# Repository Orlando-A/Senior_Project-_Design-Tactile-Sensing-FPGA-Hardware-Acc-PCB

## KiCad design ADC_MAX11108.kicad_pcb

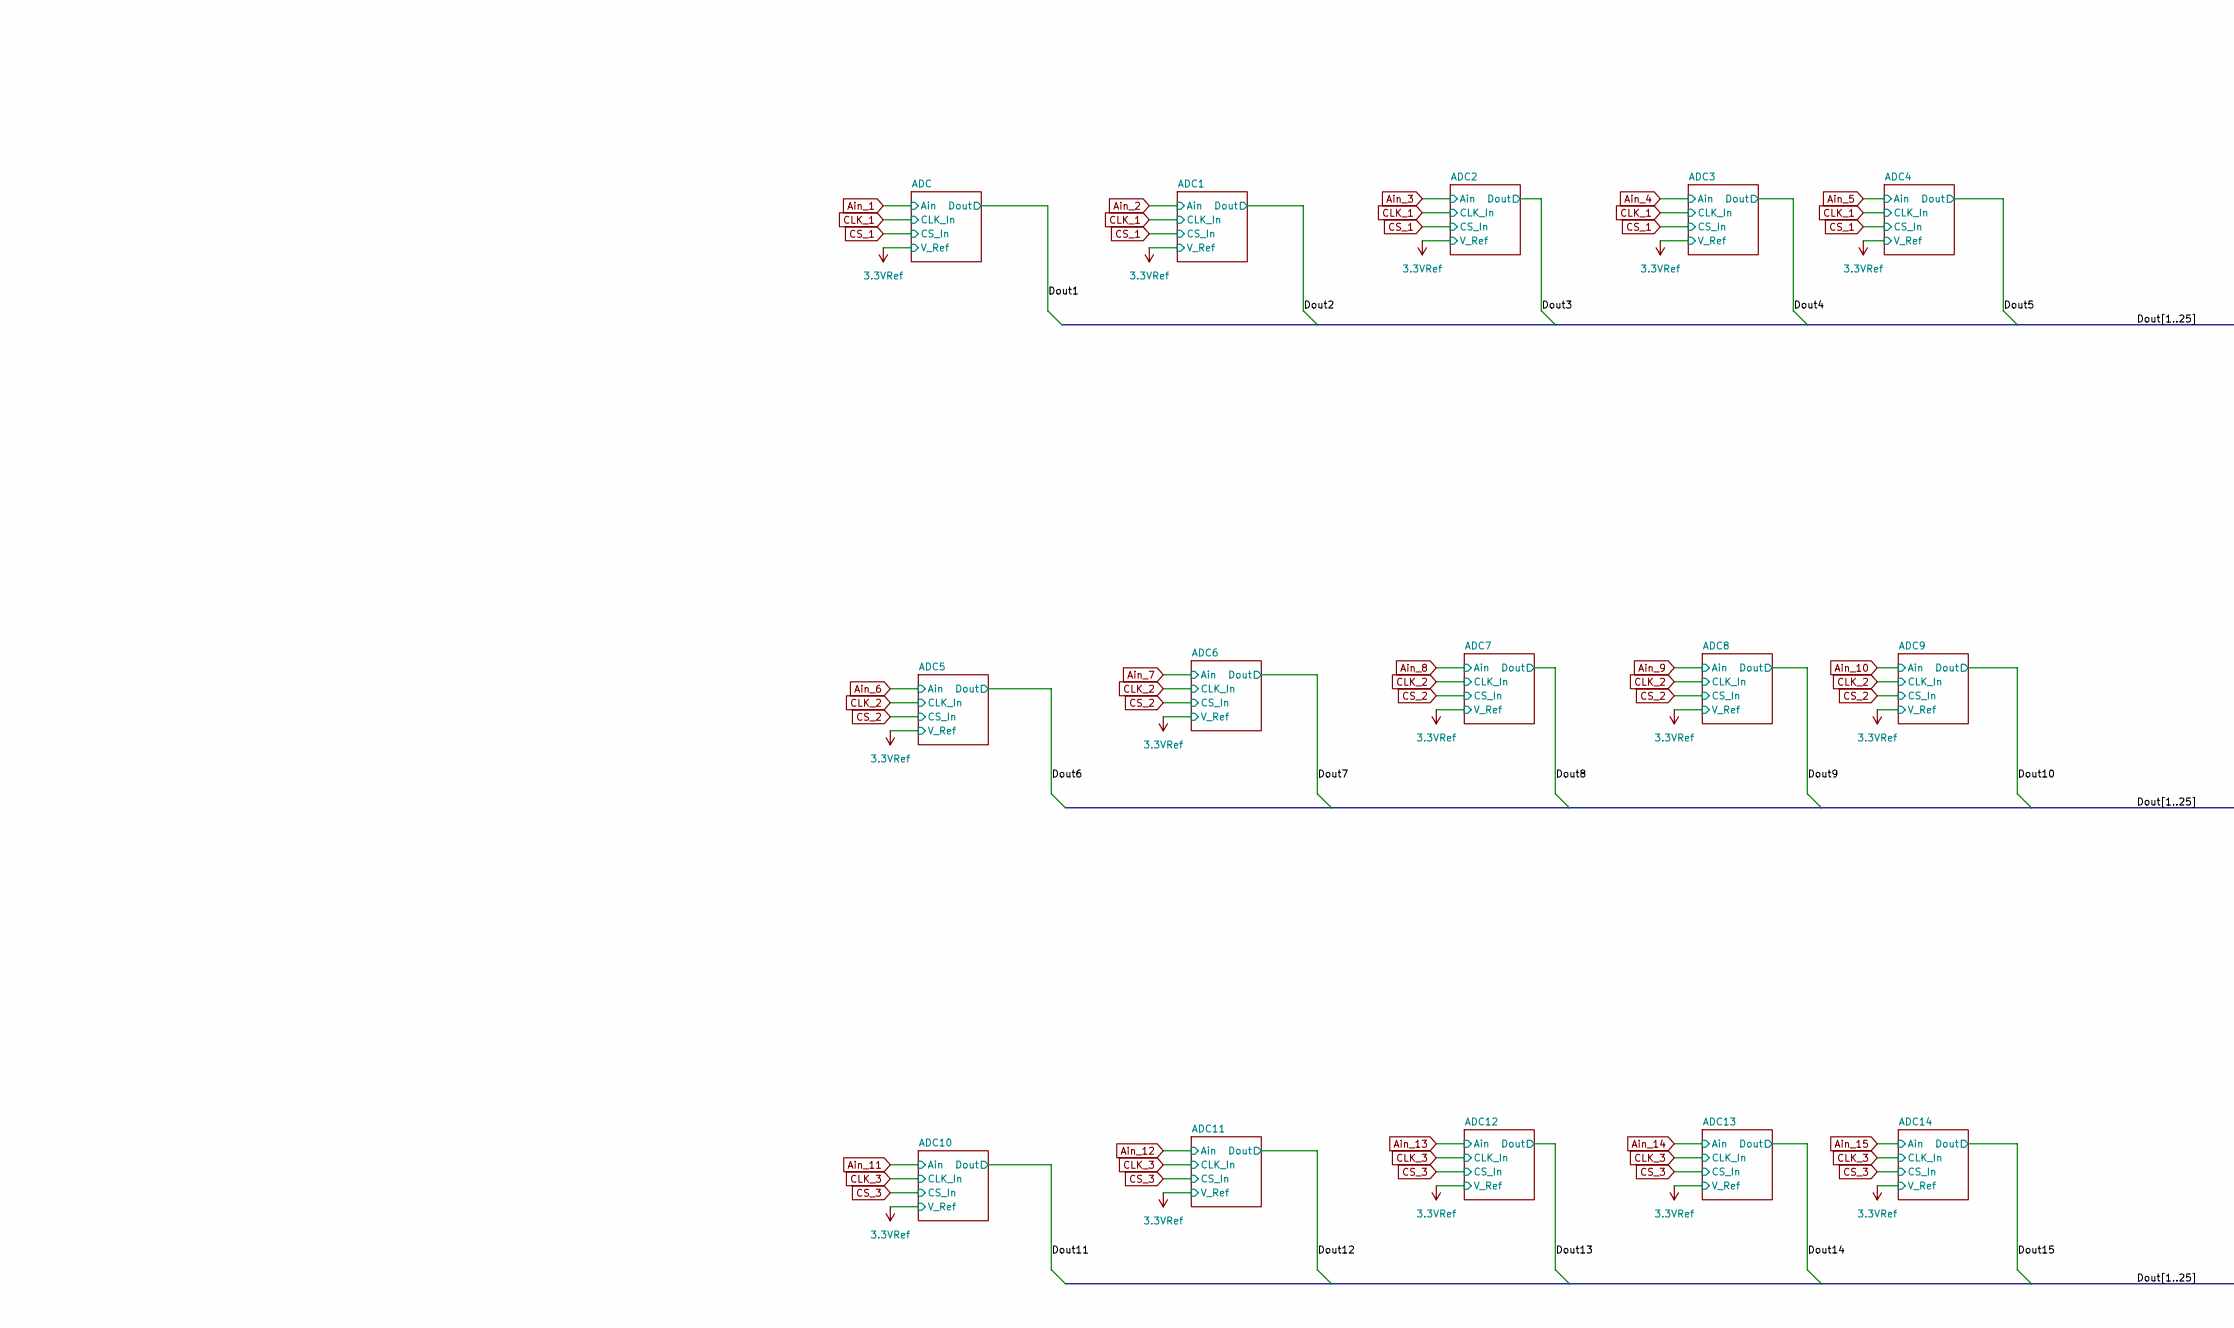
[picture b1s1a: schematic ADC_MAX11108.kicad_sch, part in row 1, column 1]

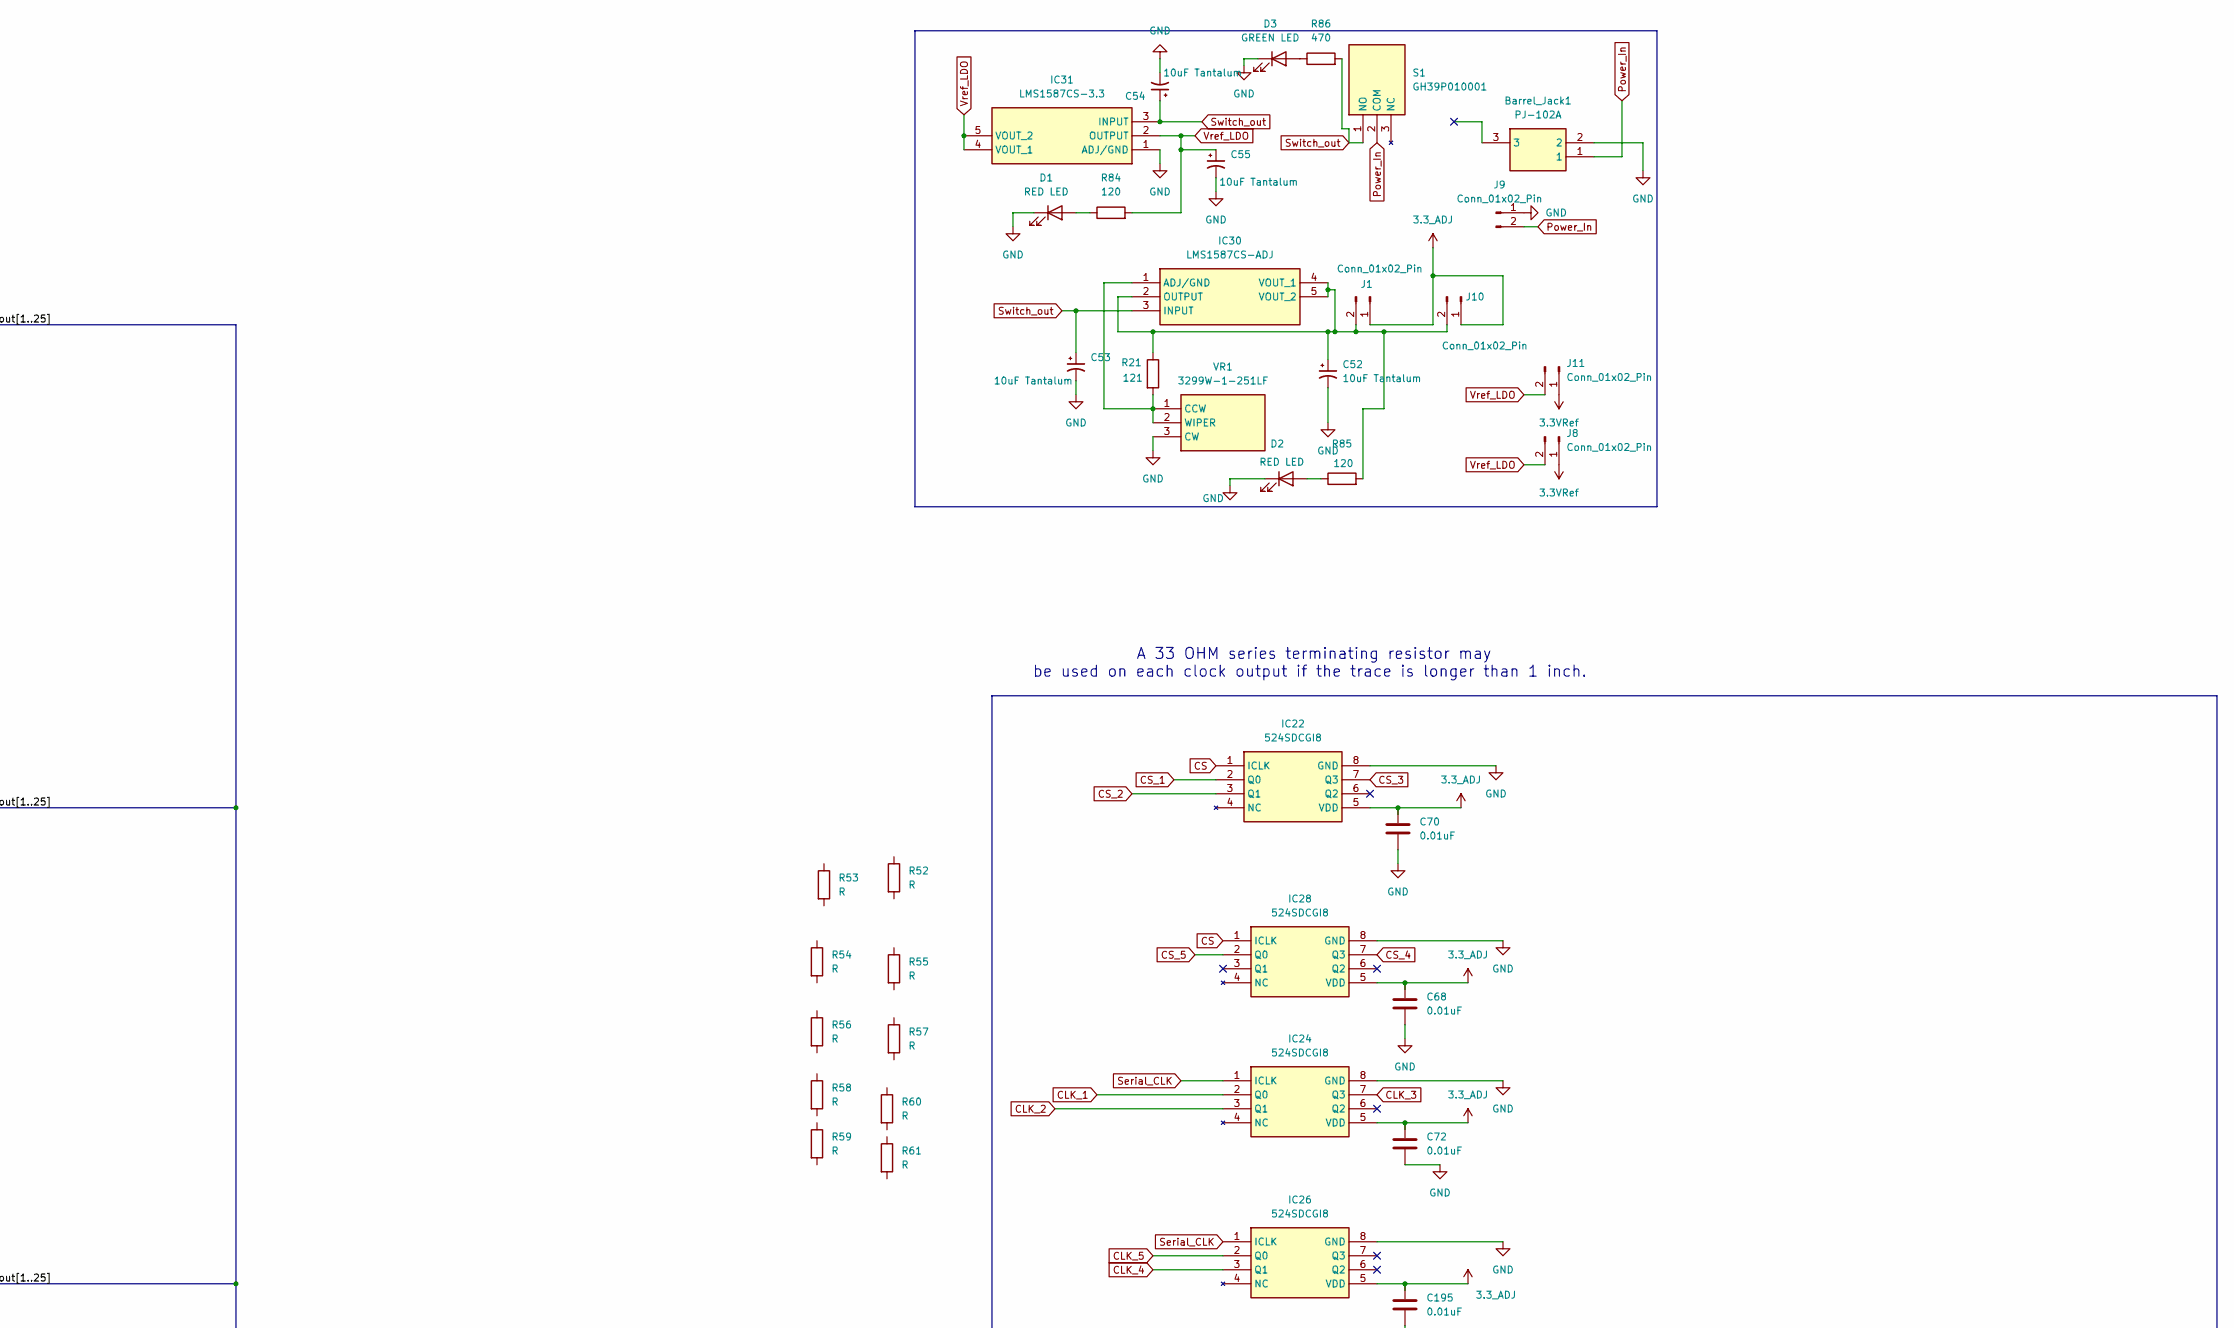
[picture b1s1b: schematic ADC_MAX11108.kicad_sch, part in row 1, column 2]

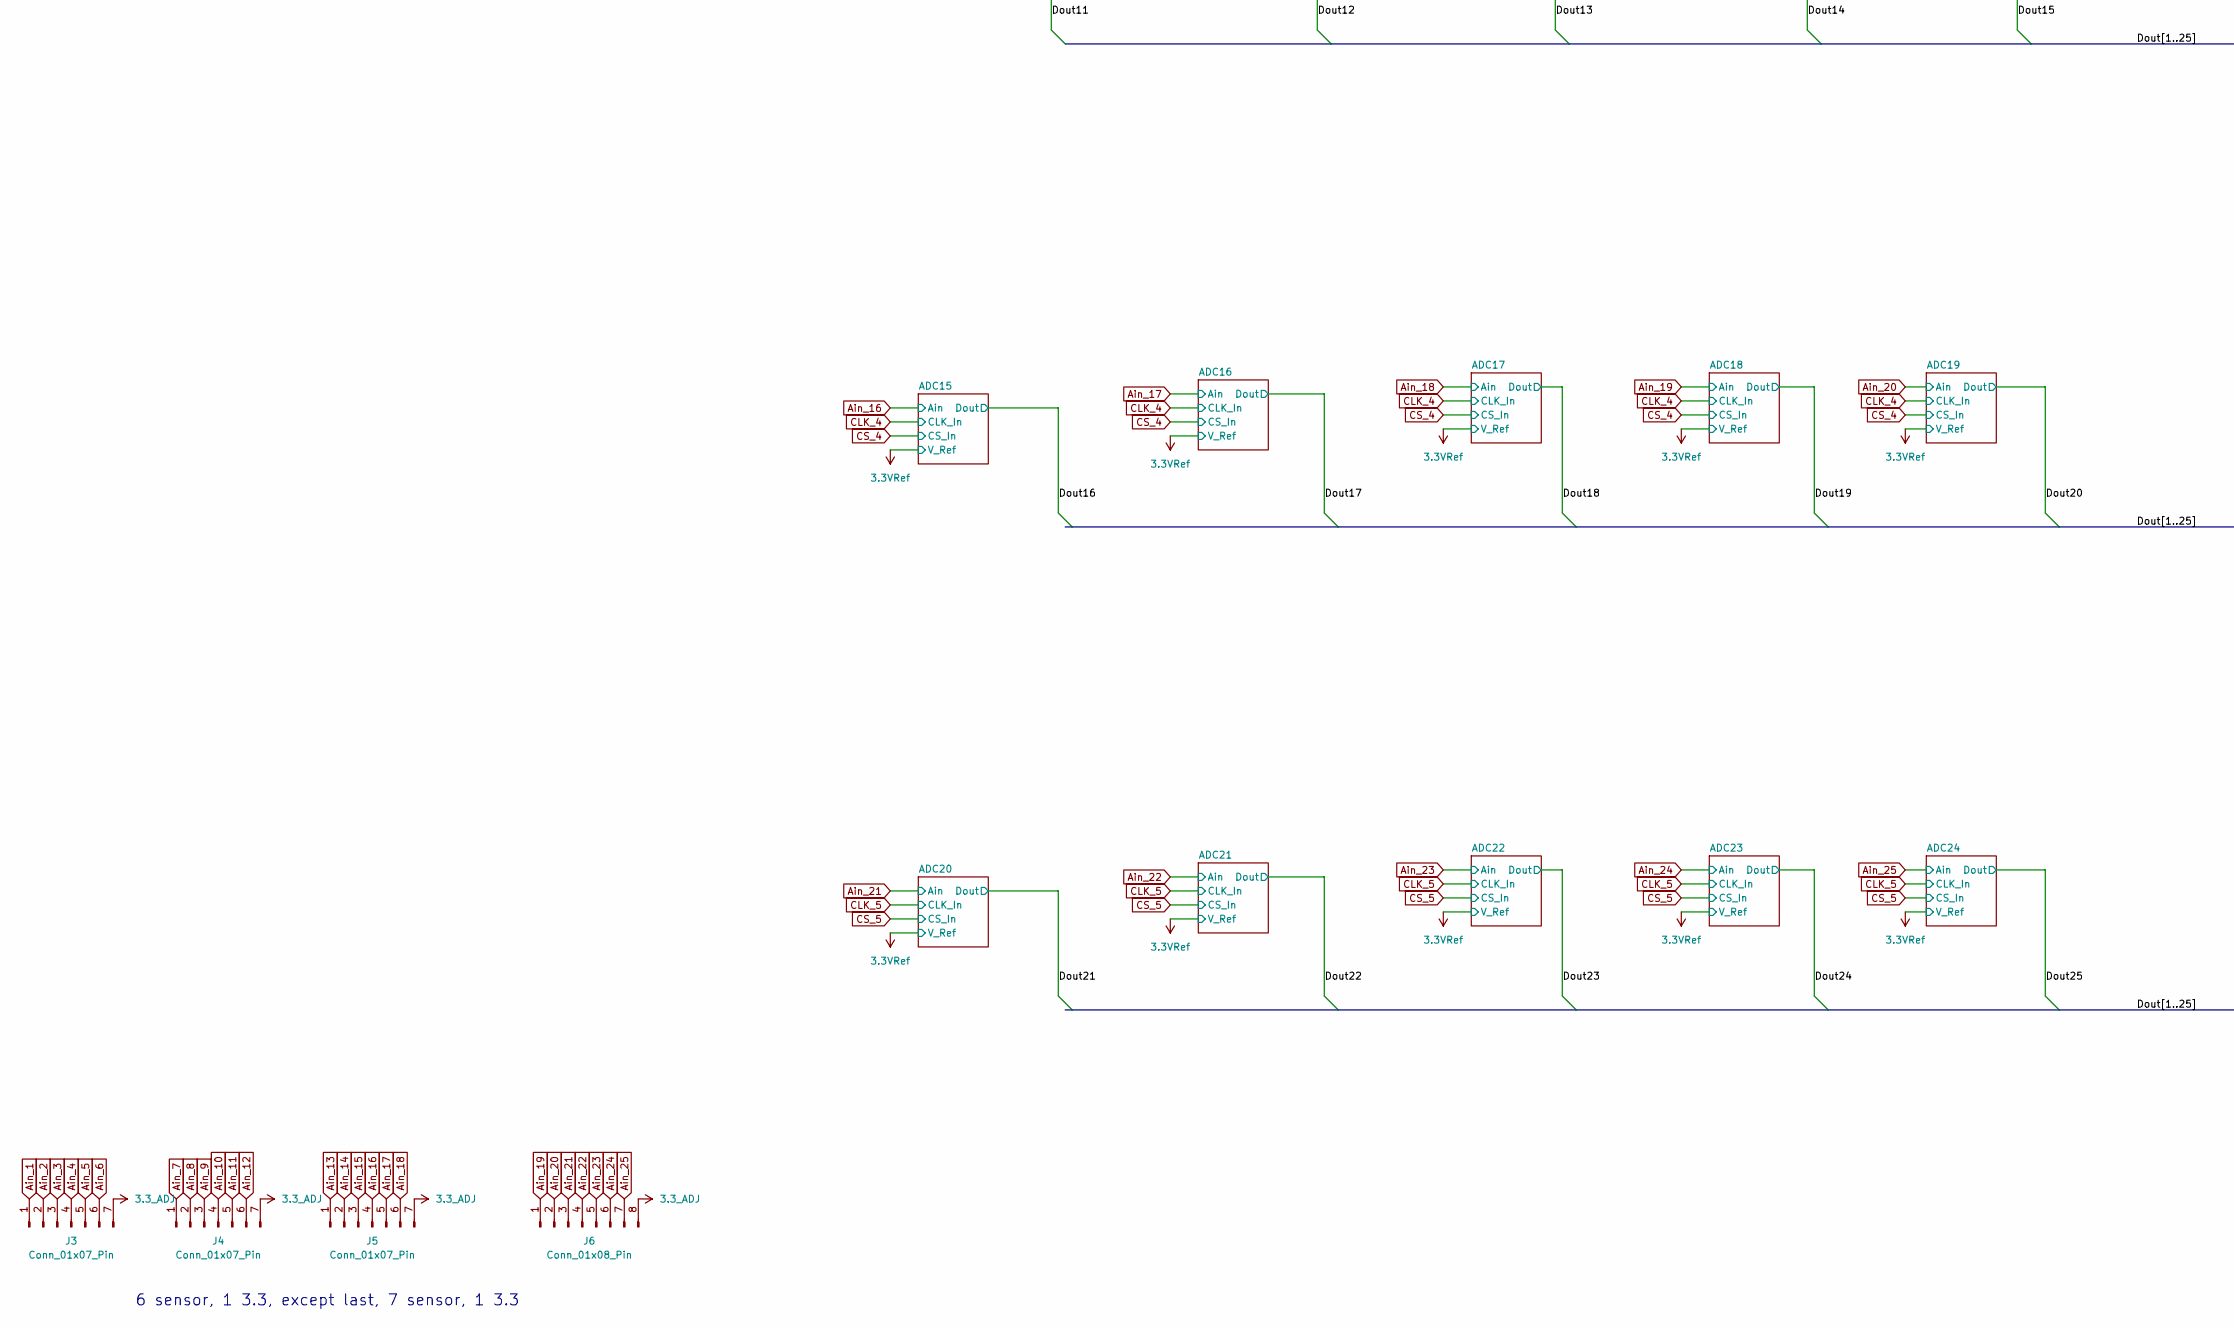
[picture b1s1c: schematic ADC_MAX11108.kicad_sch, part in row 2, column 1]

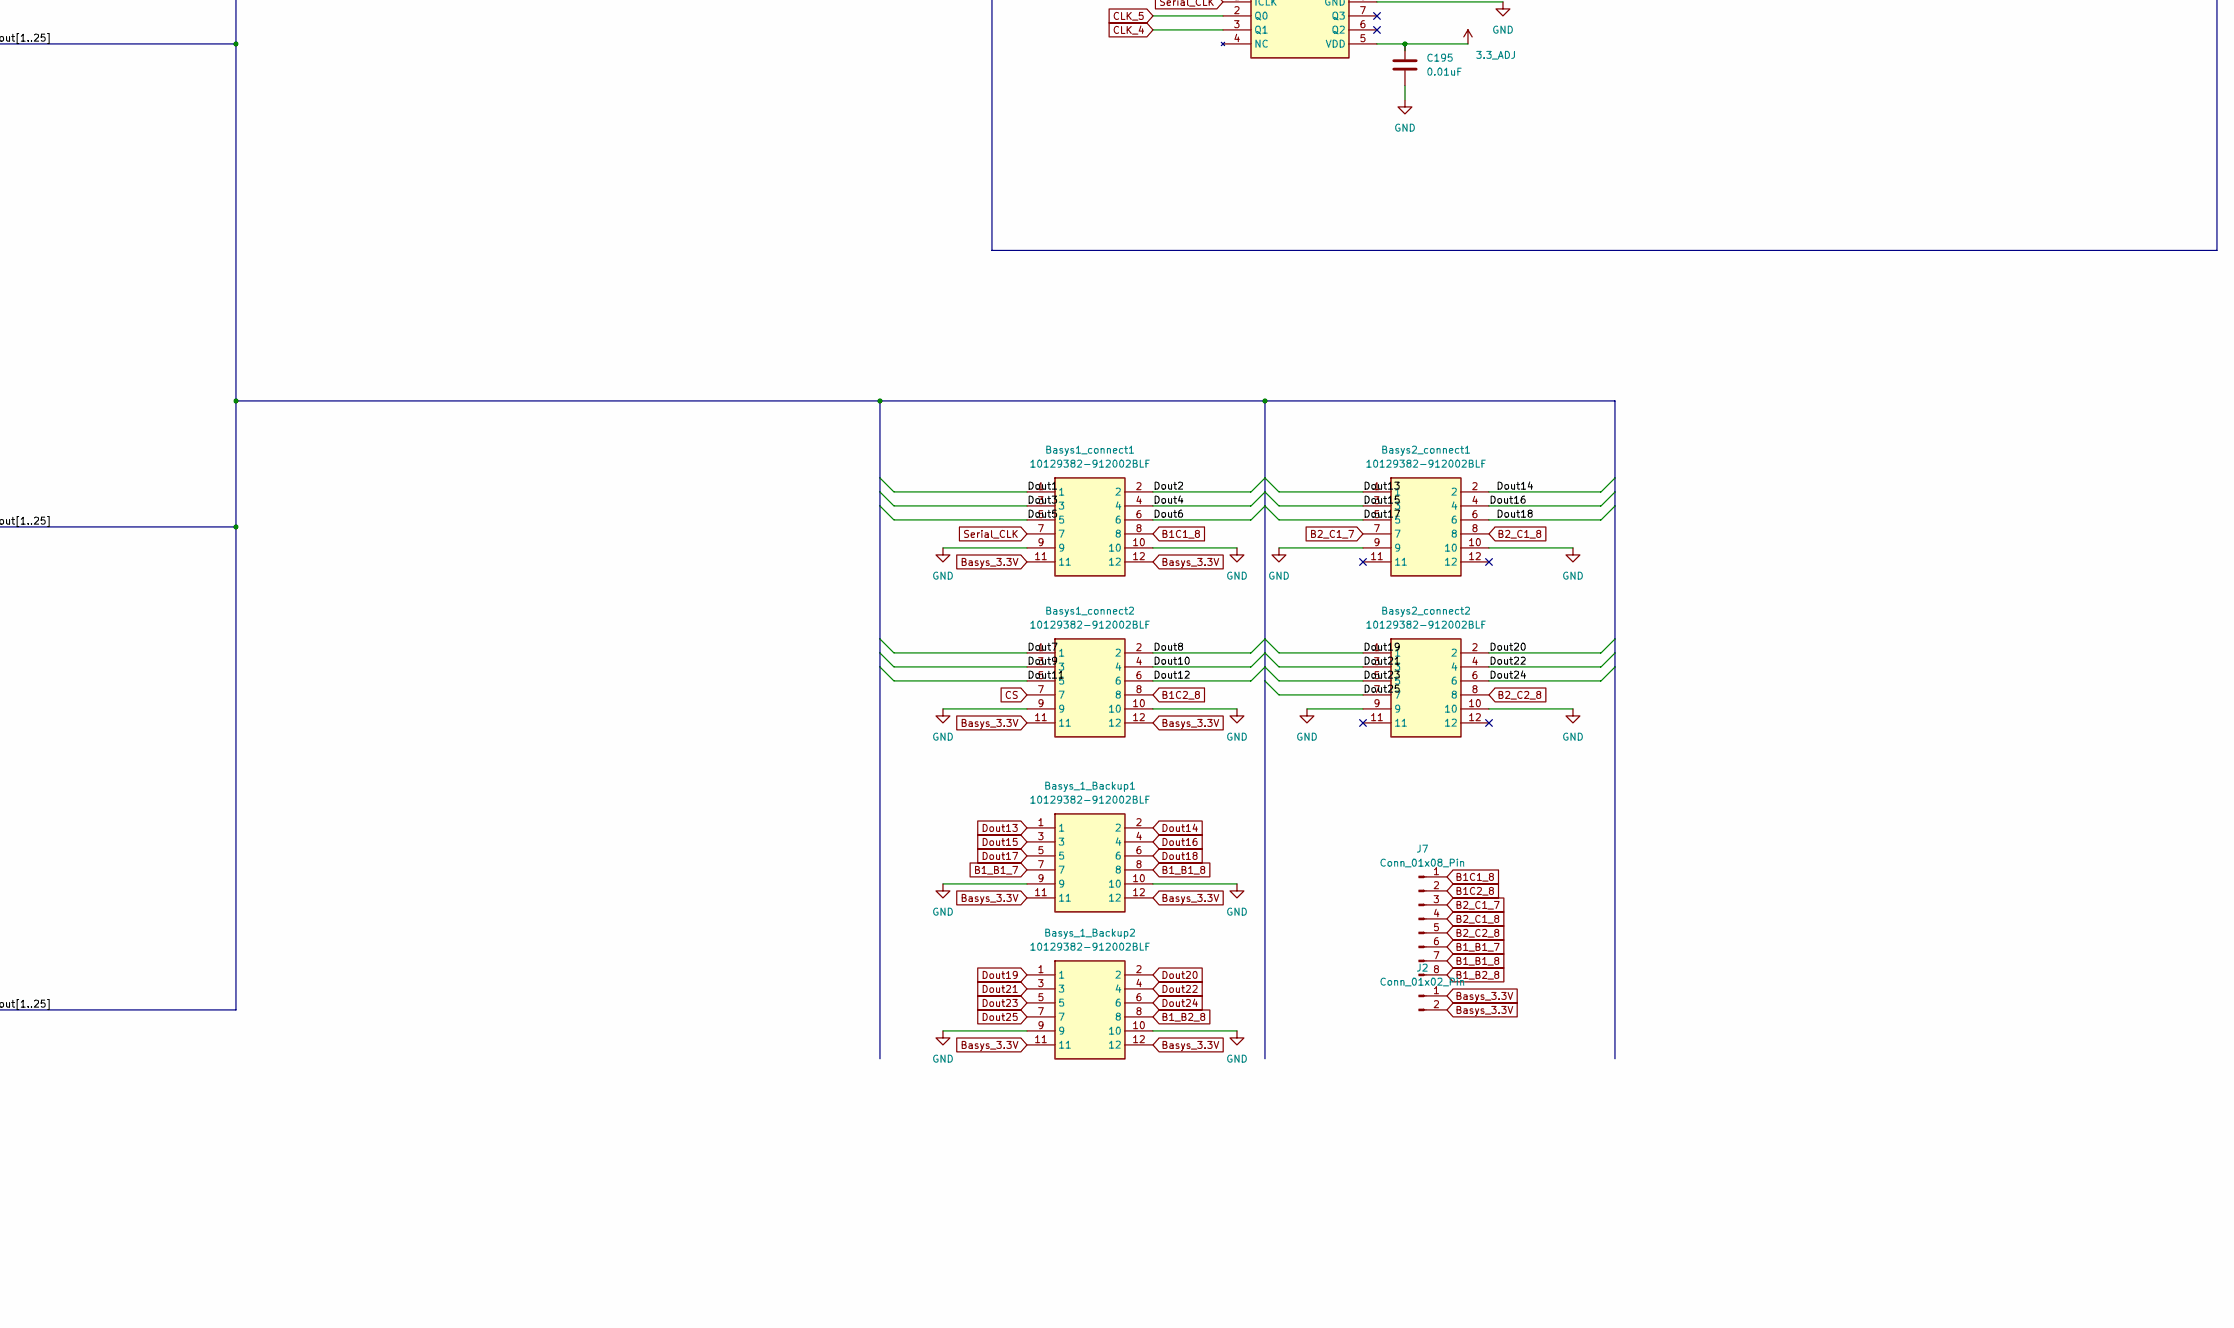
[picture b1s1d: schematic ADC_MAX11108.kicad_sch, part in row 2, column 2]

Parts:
Barrel_Jack1: PJ-102A; PJ-102AH; Manufacturer_Part_Number PJ-102A; Mouser Part Number 490-PJ-102A
Basys1_connect1, Basys1_connect2, Basys2_connect1, Basys2_connect2: 10129382-912002BLF; HDRRA12W67P254_2X6_1524X254X503P; Manufacturer_Part_Number 10129382-912002BLF
Basys_1_Backup1, Basys_1_Backup2: 10129382-912002BLF; HDRRA12W67P254_2X6_1524X254X503P; Manufacturer_Part_Number 10129382-912002BLF
C52, C53, C54, C55: 10uF Tantalum; CP_EIA-6032-28_Kemet-C_HandSolder
C68, C70, C72, C195: 0.01uF; C_0402_1005Metric_Pad0.74x0.62mm_HandSolder
D1, D2: RED LED; LED_0603_1608Metric_Pad1.05x0.95mm_HandSolder
D3: GREEN LED; LED_0603_1608Metric_Pad1.05x0.95mm_HandSolder
IC22, IC24, IC26, IC28: 524SDCGI8; SOIC127P600X175-8N; Mouser Part Number 972-524SDCGI8
IC30: LMS1587CS-ADJ; LMS1587CSXADJNOPB; Mouser Part Number 926-LS1585ACSXADJNPB
IC31: LMS1587CS-3.3; LMS1587CSXADJNOPB; Mouser Part Number 926-LS1585ACSXADJNPB
J1, J2, J8, J10, J11: Conn_01x02_Pin; PinHeader_1x02_P2.54mm_Vertical
J3, J4, J5: Conn_01x07_Pin; PinHeader_1x07_P2.54mm_Vertical
J6, J7: Conn_01x08_Pin; PinHeader_1x08_P2.54mm_Vertical
J9: Conn_01x02_Pin; JST_XA_B02B-XASK-1-A_1x02_P2.50mm_Vertical
R21: 121; R_0402_1005Metric_Pad0.72x0.64mm_HandSolder
R52, R53, R54, R55, R56, R57, R58, R59, R60, R61: R; R_0402_1005Metric_Pad0.72x0.64mm_HandSolder
R84, R85: 120; R_0603_1608Metric_Pad0.98x0.95mm_HandSolder
R86: 470; R_0603_1608Metric_Pad0.98x0.95mm_HandSolder
S1: GH39P010001; Manufacturer_Part_Number GH39P010001; Mouser Part Number 642-GH39P010001
VR1: 3299W-1-251LF; 3299W1251LF; Mouser Part Number 652-3299W-1-251LF

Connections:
3.3VRef: J8.1, J11.1; also elsewhere on the board
3.3_ADJ: C68.1, C70.1, C72.1, C195.1, IC22.5 (VDD), IC24.5 (VDD), IC26.5 (VDD), IC28.5 (VDD), J1.1, J3.7, J4.7, J5.7, J6.8, J10.1; also elsewhere on the board
/Dout1: Basys1_connect1.1; also elsewhere on the board
/Dout2: Basys1_connect1.2; also elsewhere on the board
/Dout3: Basys1_connect1.3; also elsewhere on the board
/Dout4: Basys1_connect1.4; also elsewhere on the board
/Dout5: Basys1_connect1.5; also elsewhere on the board
/Dout6: Basys1_connect1.6; also elsewhere on the board
/Dout7: Basys1_connect2.1; also elsewhere on the board
/Dout8: Basys1_connect2.2; also elsewhere on the board
/Dout9: Basys1_connect2.3; also elsewhere on the board
/Dout10: Basys1_connect2.4; also elsewhere on the board
/Dout11: Basys1_connect2.5; also elsewhere on the board
/Dout12: Basys1_connect2.6; also elsewhere on the board
Ain_1: J3.1; also elsewhere on the board
Ain_2: J3.2; also elsewhere on the board
Ain_3: J3.3; also elsewhere on the board
Ain_4: J3.4; also elsewhere on the board
Ain_5: J3.5; also elsewhere on the board
Ain_6: J3.6; also elsewhere on the board
Ain_7: J4.1; also elsewhere on the board
Ain_8: J4.2; also elsewhere on the board
Ain_9: J4.3; also elsewhere on the board
Ain_10: J4.4; also elsewhere on the board
Ain_11: J4.5; also elsewhere on the board
Ain_12: J4.6; also elsewhere on the board
Ain_13: J5.1; also elsewhere on the board
Ain_14: J5.2; also elsewhere on the board
Ain_15: J5.3; also elsewhere on the board
Ain_16: J5.4; also elsewhere on the board
Ain_17: J5.5; also elsewhere on the board
Ain_18: J5.6; also elsewhere on the board
Ain_19: J6.1; also elsewhere on the board
Ain_20: J6.2; also elsewhere on the board
Ain_21: J6.3; also elsewhere on the board
Ain_22: J6.4; also elsewhere on the board
Ain_23: J6.5; also elsewhere on the board
Ain_24: J6.6; also elsewhere on the board
Ain_25: J6.7; also elsewhere on the board
B1C1_8: Basys1_connect1.8, J7.1
B1C2_8: Basys1_connect2.8, J7.2
B1_B1_7: Basys_1_Backup1.7, J7.6
B1_B1_8: Basys_1_Backup1.8, J7.7
B1_B2_8: Basys_1_Backup2.8, J7.8
B2_C1_7: Basys2_connect1.7, J7.3
B2_C1_8: Basys2_connect1.8, J7.4
B2_C2_8: Basys2_connect2.8, J7.5
Basys_3.3V: Basys1_connect1.11, Basys1_connect1.12, Basys1_connect2.11, Basys1_connect2.12, Basys_1_Backup1.11, Basys_1_Backup1.12, Basys_1_Backup2.11, Basys_1_Backup2.12, J2.1, J2.2
CLK_1: IC24.2 (Q0); also elsewhere on the board
CLK_2: IC24.3 (Q1); also elsewhere on the board
CLK_3: IC24.7 (Q3); also elsewhere on the board
CLK_4: IC26.3 (Q1); also elsewhere on the board
CLK_5: IC26.2 (Q0); also elsewhere on the board
CS: Basys1_connect2.7, IC22.1 (ICLK), IC28.1 (ICLK)
CS_1: IC22.2 (Q0); also elsewhere on the board
CS_2: IC22.3 (Q1); also elsewhere on the board
CS_3: IC22.7 (Q3); also elsewhere on the board
CS_4: IC28.7 (Q3); also elsewhere on the board
CS_5: IC28.2 (Q0); also elsewhere on the board
Dout13: Basys2_connect1.1, Basys_1_Backup1.1; also elsewhere on the board
Dout14: Basys2_connect1.2, Basys_1_Backup1.2; also elsewhere on the board
Dout15: Basys2_connect1.3, Basys_1_Backup1.3; also elsewhere on the board
Dout16: Basys2_connect1.4, Basys_1_Backup1.4; also elsewhere on the board
Dout17: Basys2_connect1.5, Basys_1_Backup1.5; also elsewhere on the board
Dout18: Basys2_connect1.6, Basys_1_Backup1.6; also elsewhere on the board
Dout19: Basys2_connect2.1, Basys_1_Backup2.1; also elsewhere on the board
Dout20: Basys2_connect2.2, Basys_1_Backup2.2; also elsewhere on the board
Dout21: Basys2_connect2.3, Basys_1_Backup2.3; also elsewhere on the board
Dout22: Basys2_connect2.4, Basys_1_Backup2.4; also elsewhere on the board
Dout23: Basys2_connect2.5, Basys_1_Backup2.5; also elsewhere on the board
Dout24: Basys2_connect2.6, Basys_1_Backup2.6; also elsewhere on the board
Dout25: Basys2_connect2.7, Basys_1_Backup2.7; also elsewhere on the board
GND: Barrel_Jack1.2, Basys1_connect1.9, Basys1_connect1.10, Basys1_connect2.9, Basys1_connect2.10, Basys2_connect1.9, Basys2_connect1.10, Basys2_connect2.9, Basys2_connect2.10, Basys_1_Backup1.9, Basys_1_Backup1.10, Basys_1_Backup2.9, Basys_1_Backup2.10, C52.2, C53.2, C54.2, C55.2, C68.2, C70.2, C72.2, C195.2, D1.1 (K), D2.1 (K), D3.1 (K), IC22.8 (GND), IC24.8 (GND), IC26.8 (GND), IC28.8 (GND), IC31.1 (ADJ/GND), J9.1, VR1.3 (CW); also elsewhere on the board
unnamed: D1.2 (A), R84.1
unnamed: D2.2 (A), R85.1
unnamed: D3.2 (A), R86.1
unnamed: IC30.1 (ADJ/GND), R21.2, VR1.1 (CCW), VR1.2 (WIPER)
unnamed: C52.1, IC30.2 (OUTPUT), IC30.4 (VOUT_1), IC30.5 (VOUT_2), J1.2, J10.2, R21.1, R85.2
Power_In: Barrel_Jack1.1, J9.2, S1.2 (COM)
Serial_CLK: Basys1_connect1.7, IC24.1 (ICLK), IC26.1 (ICLK)
Switch_out: C53.1, C54.1, IC30.3 (INPUT), IC31.3 (INPUT), R86.2, S1.1 (NO)
Vref_LDO: C55.1, IC31.2 (OUTPUT), IC31.4 (VOUT_1), IC31.5 (VOUT_2), J8.2, J11.2, R84.2

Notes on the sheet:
6 sensor, 1 3.3, except last, 7 sensor, 1 3.3
A 33 OHM series terminating resistor may be used on each clock output if the trace is longer than 1 inch.

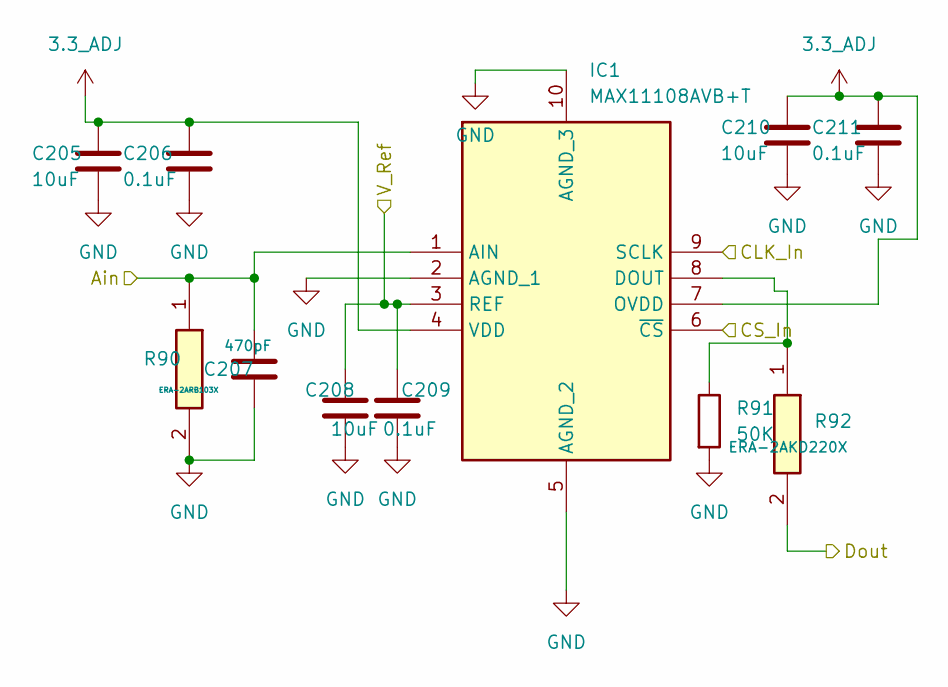
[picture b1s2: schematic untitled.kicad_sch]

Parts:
C205, C209, C210: 10uF; C_0402_1005Metric_Pad0.74x0.62mm_HandSolder
C206, C208, C211: 0.1uF; C_0402_1005Metric_Pad0.74x0.62mm_HandSolder
C207: 470pF; C_0402_1005Metric_Pad0.74x0.62mm_HandSolder
IC1: MAX11108AVB+T; QFN50P160X210X50-10N-D; Manufacturer_Part_Number MAX11108AVB+T; Mouser Part Number 700-MAX11108AVB+T
R90: ERA-2ARB103X; R_0402_1005Metric_Pad0.72x0.64mm_HandSolder; Mouser Part Number 667-ERA-2ARB103X
R91: 50K; R_0402_1005Metric_Pad0.72x0.64mm_HandSolder
R92: ERA-2AKD220X; R_0402_1005Metric_Pad0.72x0.64mm_HandSolder; Manufacturer_Part_Number ERA-2AKD220X

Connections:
3.3VRef: C208.1, C209.1, IC1.3 (REF); also elsewhere on the board
3.3_ADJ: C205.1, C206.1, C210.1, C211.1, IC1.4 (VDD), IC1.7 (OVDD); also elsewhere on the board
/Dout1: R92.2; also elsewhere on the board
Ain_1: C207.1, IC1.1 (AIN), R90.1; also elsewhere on the board
CLK_1: IC1.9 (SCLK); also elsewhere on the board
CS_1: IC1.6 (~CS); also elsewhere on the board
GND: C205.2, C206.2, C207.2, C208.2, C209.2, C210.2, C211.2, IC1.2 (AGND_1), IC1.5 (AGND_2), IC1.10 (AGND_3), R90.2, R91.2; also elsewhere on the board
unnamed: IC1.8 (DOUT), R91.1, R92.1

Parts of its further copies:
C1, C3, C7, C8, C10, C14, C15, C17, C21, C22, C24, C30, C31, C33, C37, C38, C40, C44, C45, C47, C51, C62, C64, C65, C75, C79, C80, C82, C86, C87, C89, C93, C94, C96, C100, C101, C103, C107, C108, C110, C114, C115, C117, C121, C122, C124, C128, C129, C131, C135, C136, C138, C142, C143, C145, C149, C150, C152, C156, C157, C159, C163, C164, C166, C170, C171, C173, C177, C178, C180, C184, C185: 10uF; C_0402_1005Metric_Pad0.74x0.62mm_HandSolder
C2, C4, C6, C9, C11, C13, C16, C18, C20, C23, C25, C27, C29, C32, C34, C36, C39, C41, C43, C46, C48, C50, C63, C74, C76, C78, C81, C83, C85, C88, C90, C92, C95, C97, C99, C102, C104, C106, C109, C111, C113, C116, C118, C120, C123, C125, C127, C130, C132, C134, C137, C139, C141, C144, C146, C148, C151, C153, C155, C158, C160, C162, C165, C167, C169, C172, C174, C176, C179, C181, C183, C186: 0.1uF; C_0402_1005Metric_Pad0.74x0.62mm_HandSolder
C5, C12, C19, C26, C28, C35, C42, C49, C77, C84, C91, C98, C105, C112, C119, C126, C133, C140, C147, C154, C161, C168, C175, C182: 470pF; C_0402_1005Metric_Pad0.74x0.62mm_HandSolder
IC2, IC3, IC4, IC5, IC6, IC7, IC8, IC9, IC10, IC11, IC12, IC13, IC14, IC15, IC16, IC17, IC18, IC19, IC20, IC21, IC23, IC25, IC27, IC29: MAX11108AVB+T; QFN50P160X210X50-10N-D; Manufacturer_Part_Number MAX11108AVB+T; Mouser Part Number 700-MAX11108AVB+T
R1, R3, R6, R9, R12, R15, R18, R22, R25, R29, R32, R35, R38, R41, R44, R47, R50, R63, R66, R69, R72, R75, R78, R81: ERA-2ARB103X; R_0402_1005Metric_Pad0.72x0.64mm_HandSolder; Mouser Part Number 667-ERA-2ARB103X
R2, R4, R7, R10, R13, R16, R19, R23, R27, R30, R33, R36, R39, R42, R45, R48, R51, R64, R67, R70, R73, R76, R79, R82: 50K; R_0402_1005Metric_Pad0.72x0.64mm_HandSolder
R5, R8, R11, R14, R17, R20, R24, R26, R28, R31, R34, R37, R40, R43, R46, R49, R62, R65, R68, R71, R74, R77, R80, R83: ERA-2AKD220X; R_0402_1005Metric_Pad0.72x0.64mm_HandSolder; Manufacturer_Part_Number ERA-2AKD220X

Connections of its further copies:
3.3VRef: C6.1, C7.1, C13.1, C14.1, C20.1, C21.1, C27.1, C29.1, C30.1, C36.1, C37.1, C43.1, C44.1, C50.1, C51.1, C64.1, C78.1, C79.1, C85.1, C86.1, C92.1, C93.1, C99.1, C100.1, C106.1, C107.1, C113.1, C114.1, C120.1, C121.1, C127.1, C128.1, C134.1, C135.1, C141.1, C142.1, C148.1, C149.1, C155.1, C156.1, C162.1, C163.1, C169.1, C170.1, C176.1, C177.1, C183.1, C184.1, IC2.3 (REF), IC3.3 (REF), IC4.3 (REF), IC5.3 (REF), IC6.3 (REF), IC7.3 (REF), IC8.3 (REF), IC9.3 (REF), IC10.3 (REF), IC11.3 (REF), IC12.3 (REF), IC13.3 (REF), IC14.3 (REF), IC15.3 (REF), IC16.3 (REF), IC17.3 (REF), IC18.3 (REF), IC19.3 (REF), IC20.3 (REF), IC21.3 (REF), IC23.3 (REF), IC25.3 (REF), IC27.3 (REF), IC29.3 (REF); also elsewhere on the board
3.3_ADJ: C1.1, C2.1, C3.1, C4.1, C8.1, C9.1, C10.1, C11.1, C15.1, C16.1, C17.1, C18.1, C22.1, C23.1, C24.1, C25.1, C31.1, C32.1, C33.1, C34.1, C38.1, C39.1, C40.1, C41.1, C45.1, C46.1, C47.1, C48.1, C62.1, C63.1, C65.1, C74.1, C75.1, C76.1, C80.1, C81.1, C82.1, C83.1, C87.1, C88.1, C89.1, C90.1, C94.1, C95.1, C96.1, C97.1, C101.1, C102.1, C103.1, C104.1, C108.1, C109.1, C110.1, C111.1, C115.1, C116.1, C117.1, C118.1, C122.1, C123.1, C124.1, C125.1, C129.1, C130.1, C131.1, C132.1, C136.1, C137.1, C138.1, C139.1, C143.1, C144.1, C145.1, C146.1, C150.1, C151.1, C152.1, C153.1, C157.1, C158.1, C159.1, C160.1, C164.1, C165.1, C166.1, C167.1, C171.1, C172.1, C173.1, C174.1, C178.1, C179.1, C180.1, C181.1, C185.1, C186.1, IC2.4 (VDD), IC2.7 (OVDD), IC3.4 (VDD), IC3.7 (OVDD), IC4.4 (VDD), IC4.7 (OVDD), IC5.4 (VDD), IC5.7 (OVDD), IC6.4 (VDD), IC6.7 (OVDD), IC7.4 (VDD), IC7.7 (OVDD), IC8.4 (VDD), IC8.7 (OVDD), IC9.4 (VDD), IC9.7 (OVDD), IC10.4 (VDD), IC10.7 (OVDD), IC11.4 (VDD), IC11.7 (OVDD), IC12.4 (VDD), IC12.7 (OVDD), IC13.4 (VDD), IC13.7 (OVDD), IC14.4 (VDD), IC14.7 (OVDD), IC15.4 (VDD), IC15.7 (OVDD), IC16.4 (VDD), IC16.7 (OVDD), IC17.4 (VDD), IC17.7 (OVDD), IC18.4 (VDD), IC18.7 (OVDD), IC19.4 (VDD), IC19.7 (OVDD), IC20.4 (VDD), IC20.7 (OVDD), IC21.4 (VDD), IC21.7 (OVDD), IC23.4 (VDD), IC23.7 (OVDD), IC25.4 (VDD), IC25.7 (OVDD), IC27.4 (VDD), IC27.7 (OVDD), IC29.4 (VDD), IC29.7 (OVDD); also elsewhere on the board
/Dout2: R26.2; also elsewhere on the board
/Dout3: R5.2; also elsewhere on the board
/Dout4: R8.2; also elsewhere on the board
/Dout5: R11.2; also elsewhere on the board
/Dout6: R14.2; also elsewhere on the board
/Dout7: R17.2; also elsewhere on the board
/Dout8: R20.2; also elsewhere on the board
/Dout9: R24.2; also elsewhere on the board
/Dout10: R28.2; also elsewhere on the board
/Dout11: R31.2; also elsewhere on the board
/Dout12: R34.2; also elsewhere on the board
Ain_2: C26.1, IC2.1 (AIN), R1.1; also elsewhere on the board
Ain_3: C5.1, IC3.1 (AIN), R3.1; also elsewhere on the board
Ain_4: C12.1, IC4.1 (AIN), R6.1; also elsewhere on the board
Ain_5: C19.1, IC5.1 (AIN), R9.1; also elsewhere on the board
Ain_6: C28.1, IC6.1 (AIN), R12.1; also elsewhere on the board
Ain_7: C35.1, IC7.1 (AIN), R15.1; also elsewhere on the board
Ain_8: C42.1, IC8.1 (AIN), R18.1; also elsewhere on the board
Ain_9: C49.1, IC9.1 (AIN), R22.1; also elsewhere on the board
Ain_10: C77.1, IC10.1 (AIN), R25.1; also elsewhere on the board
Ain_11: C84.1, IC11.1 (AIN), R29.1; also elsewhere on the board
Ain_12: C91.1, IC12.1 (AIN), R32.1; also elsewhere on the board
Ain_13: C98.1, IC13.1 (AIN), R35.1; also elsewhere on the board
Ain_14: C105.1, IC14.1 (AIN), R38.1; also elsewhere on the board
Ain_15: C112.1, IC15.1 (AIN), R41.1; also elsewhere on the board
Ain_16: C119.1, IC16.1 (AIN), R44.1; also elsewhere on the board
Ain_17: C126.1, IC17.1 (AIN), R47.1; also elsewhere on the board
Ain_18: C133.1, IC18.1 (AIN), R50.1; also elsewhere on the board
Ain_19: C140.1, IC19.1 (AIN), R63.1; also elsewhere on the board
Ain_20: C147.1, IC20.1 (AIN), R66.1; also elsewhere on the board
Ain_21: C154.1, IC21.1 (AIN), R69.1; also elsewhere on the board
Ain_22: C161.1, IC23.1 (AIN), R72.1; also elsewhere on the board
Ain_23: C168.1, IC25.1 (AIN), R75.1; also elsewhere on the board
Ain_24: C175.1, IC27.1 (AIN), R78.1; also elsewhere on the board
Ain_25: C182.1, IC29.1 (AIN), R81.1; also elsewhere on the board
CLK_1: IC2.9 (SCLK), IC3.9 (SCLK), IC4.9 (SCLK), IC5.9 (SCLK); also elsewhere on the board
CLK_2: IC6.9 (SCLK), IC7.9 (SCLK), IC8.9 (SCLK), IC9.9 (SCLK), IC10.9 (SCLK); also elsewhere on the board
CLK_3: IC11.9 (SCLK), IC12.9 (SCLK), IC13.9 (SCLK), IC14.9 (SCLK), IC15.9 (SCLK); also elsewhere on the board
CLK_4: IC16.9 (SCLK), IC17.9 (SCLK), IC18.9 (SCLK), IC19.9 (SCLK), IC20.9 (SCLK); also elsewhere on the board
CLK_5: IC21.9 (SCLK), IC23.9 (SCLK), IC25.9 (SCLK), IC27.9 (SCLK), IC29.9 (SCLK); also elsewhere on the board
CS_1: IC2.6 (~CS), IC3.6 (~CS), IC4.6 (~CS), IC5.6 (~CS); also elsewhere on the board
CS_2: IC6.6 (~CS), IC7.6 (~CS), IC8.6 (~CS), IC9.6 (~CS), IC10.6 (~CS); also elsewhere on the board
CS_3: IC11.6 (~CS), IC12.6 (~CS), IC13.6 (~CS), IC14.6 (~CS), IC15.6 (~CS); also elsewhere on the board
CS_4: IC16.6 (~CS), IC17.6 (~CS), IC18.6 (~CS), IC19.6 (~CS), IC20.6 (~CS); also elsewhere on the board
CS_5: IC21.6 (~CS), IC23.6 (~CS), IC25.6 (~CS), IC27.6 (~CS), IC29.6 (~CS); also elsewhere on the board
Dout13: R37.2; also elsewhere on the board
Dout14: R40.2; also elsewhere on the board
Dout15: R43.2; also elsewhere on the board
Dout16: R46.2; also elsewhere on the board
Dout17: R49.2; also elsewhere on the board
Dout18: R62.2; also elsewhere on the board
Dout19: R65.2; also elsewhere on the board
Dout20: R68.2; also elsewhere on the board
Dout21: R71.2; also elsewhere on the board
Dout22: R74.2; also elsewhere on the board
Dout23: R77.2; also elsewhere on the board
Dout24: R80.2; also elsewhere on the board
Dout25: R83.2; also elsewhere on the board
GND: C1.2, C2.2, C3.2, C4.2, C5.2, C6.2, C7.2, C8.2, C9.2, C10.2, C11.2, C12.2, C13.2, C14.2, C15.2, C16.2, C17.2, C18.2, C19.2, C20.2, C21.2, C22.2, C23.2, C24.2, C25.2, C26.2, C27.2, C28.2, C29.2, C30.2, C31.2, C32.2, C33.2, C34.2, C35.2, C36.2, C37.2, C38.2, C39.2, C40.2, C41.2, C42.2, C43.2, C44.2, C45.2, C46.2, C47.2, C48.2, C49.2, C50.2, C51.2, C62.2, C63.2, C64.2, C65.2, C74.2, C75.2, C76.2, C77.2, C78.2, C79.2, C80.2, C81.2, C82.2, C83.2, C84.2, C85.2, C86.2, C87.2, C88.2, C89.2, C90.2, C91.2, C92.2, C93.2, C94.2, C95.2, C96.2, C97.2, C98.2, C99.2, C100.2, C101.2, C102.2, C103.2, C104.2, C105.2, C106.2, C107.2, C108.2, C109.2, C110.2, C111.2, C112.2, C113.2, C114.2, C115.2, C116.2, C117.2, C118.2, C119.2, C120.2, C121.2, C122.2, C123.2, C124.2, C125.2, C126.2, C127.2, C128.2, C129.2, C130.2, C131.2, C132.2, C133.2, C134.2, C135.2, C136.2, C137.2, C138.2, C139.2, C140.2, C141.2, C142.2, C143.2, C144.2, C145.2, C146.2, C147.2, C148.2, C149.2, C150.2, C151.2, C152.2, C153.2, C154.2, C155.2, C156.2, C157.2, C158.2, C159.2, C160.2, C161.2, C162.2, C163.2, C164.2, C165.2, C166.2, C167.2, C168.2, C169.2, C170.2, C171.2, C172.2, C173.2, C174.2, C175.2, C176.2, C177.2, C178.2, C179.2, C180.2, C181.2, C182.2, C183.2, C184.2, C185.2, C186.2, IC2.2 (AGND_1), IC2.5 (AGND_2), IC2.10 (AGND_3), IC3.2 (AGND_1), IC3.5 (AGND_2), IC3.10 (AGND_3), IC4.2 (AGND_1), IC4.5 (AGND_2), IC4.10 (AGND_3), IC5.2 (AGND_1), IC5.5 (AGND_2), IC5.10 (AGND_3), IC6.2 (AGND_1), IC6.5 (AGND_2), IC6.10 (AGND_3), IC7.2 (AGND_1), IC7.5 (AGND_2), IC7.10 (AGND_3), IC8.2 (AGND_1), IC8.5 (AGND_2), IC8.10 (AGND_3), IC9.2 (AGND_1), IC9.5 (AGND_2), IC9.10 (AGND_3), IC10.2 (AGND_1), IC10.5 (AGND_2), IC10.10 (AGND_3), IC11.2 (AGND_1), IC11.5 (AGND_2), IC11.10 (AGND_3), IC12.2 (AGND_1), IC12.5 (AGND_2), IC12.10 (AGND_3), IC13.2 (AGND_1), IC13.5 (AGND_2), IC13.10 (AGND_3), IC14.2 (AGND_1), IC14.5 (AGND_2), IC14.10 (AGND_3), IC15.2 (AGND_1), IC15.5 (AGND_2), IC15.10 (AGND_3), IC16.2 (AGND_1), IC16.5 (AGND_2), IC16.10 (AGND_3), IC17.2 (AGND_1), IC17.5 (AGND_2), IC17.10 (AGND_3), IC18.2 (AGND_1), IC18.5 (AGND_2), IC18.10 (AGND_3), IC19.2 (AGND_1), IC19.5 (AGND_2), IC19.10 (AGND_3), IC20.2 (AGND_1), IC20.5 (AGND_2), IC20.10 (AGND_3), IC21.2 (AGND_1), IC21.5 (AGND_2), IC21.10 (AGND_3), IC23.2 (AGND_1), IC23.5 (AGND_2), IC23.10 (AGND_3), IC25.2 (AGND_1), IC25.5 (AGND_2), IC25.10 (AGND_3), IC27.2 (AGND_1), IC27.5 (AGND_2), IC27.10 (AGND_3), IC29.2 (AGND_1), IC29.5 (AGND_2), IC29.10 (AGND_3), R1.2, R2.2, R3.2, R4.2, R6.2, R7.2, R9.2, R10.2, R12.2, R13.2, R15.2, R16.2, R18.2, R19.2, R22.2, R23.2, R25.2, R27.2, R29.2, R30.2, R32.2, R33.2, R35.2, R36.2, R38.2, R39.2, R41.2, R42.2, R44.2, R45.2, R47.2, R48.2, R50.2, R51.2, R63.2, R64.2, R66.2, R67.2, R69.2, R70.2, R72.2, R73.2, R75.2, R76.2, R78.2, R79.2, R81.2, R82.2; also elsewhere on the board
unnamed: IC2.8 (DOUT), R2.1, R26.1
unnamed: IC3.8 (DOUT), R4.1, R5.1
unnamed: IC4.8 (DOUT), R7.1, R8.1
unnamed: IC5.8 (DOUT), R10.1, R11.1
unnamed: IC6.8 (DOUT), R13.1, R14.1
unnamed: IC7.8 (DOUT), R16.1, R17.1
unnamed: IC8.8 (DOUT), R19.1, R20.1
unnamed: IC9.8 (DOUT), R23.1, R24.1
unnamed: IC10.8 (DOUT), R27.1, R28.1
unnamed: IC11.8 (DOUT), R30.1, R31.1
unnamed: IC12.8 (DOUT), R33.1, R34.1
unnamed: IC13.8 (DOUT), R36.1, R37.1
unnamed: IC14.8 (DOUT), R39.1, R40.1
unnamed: IC15.8 (DOUT), R42.1, R43.1
unnamed: IC16.8 (DOUT), R45.1, R46.1
unnamed: IC17.8 (DOUT), R48.1, R49.1
unnamed: IC18.8 (DOUT), R51.1, R62.1
unnamed: IC19.8 (DOUT), R64.1, R65.1
unnamed: IC20.8 (DOUT), R67.1, R68.1
unnamed: IC21.8 (DOUT), R70.1, R71.1
unnamed: IC23.8 (DOUT), R73.1, R74.1
unnamed: IC25.8 (DOUT), R76.1, R77.1
unnamed: IC27.8 (DOUT), R79.1, R80.1
unnamed: IC29.8 (DOUT), R82.1, R83.1
